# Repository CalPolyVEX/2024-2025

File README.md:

# 2024-2025

Code for 2024-2025 year

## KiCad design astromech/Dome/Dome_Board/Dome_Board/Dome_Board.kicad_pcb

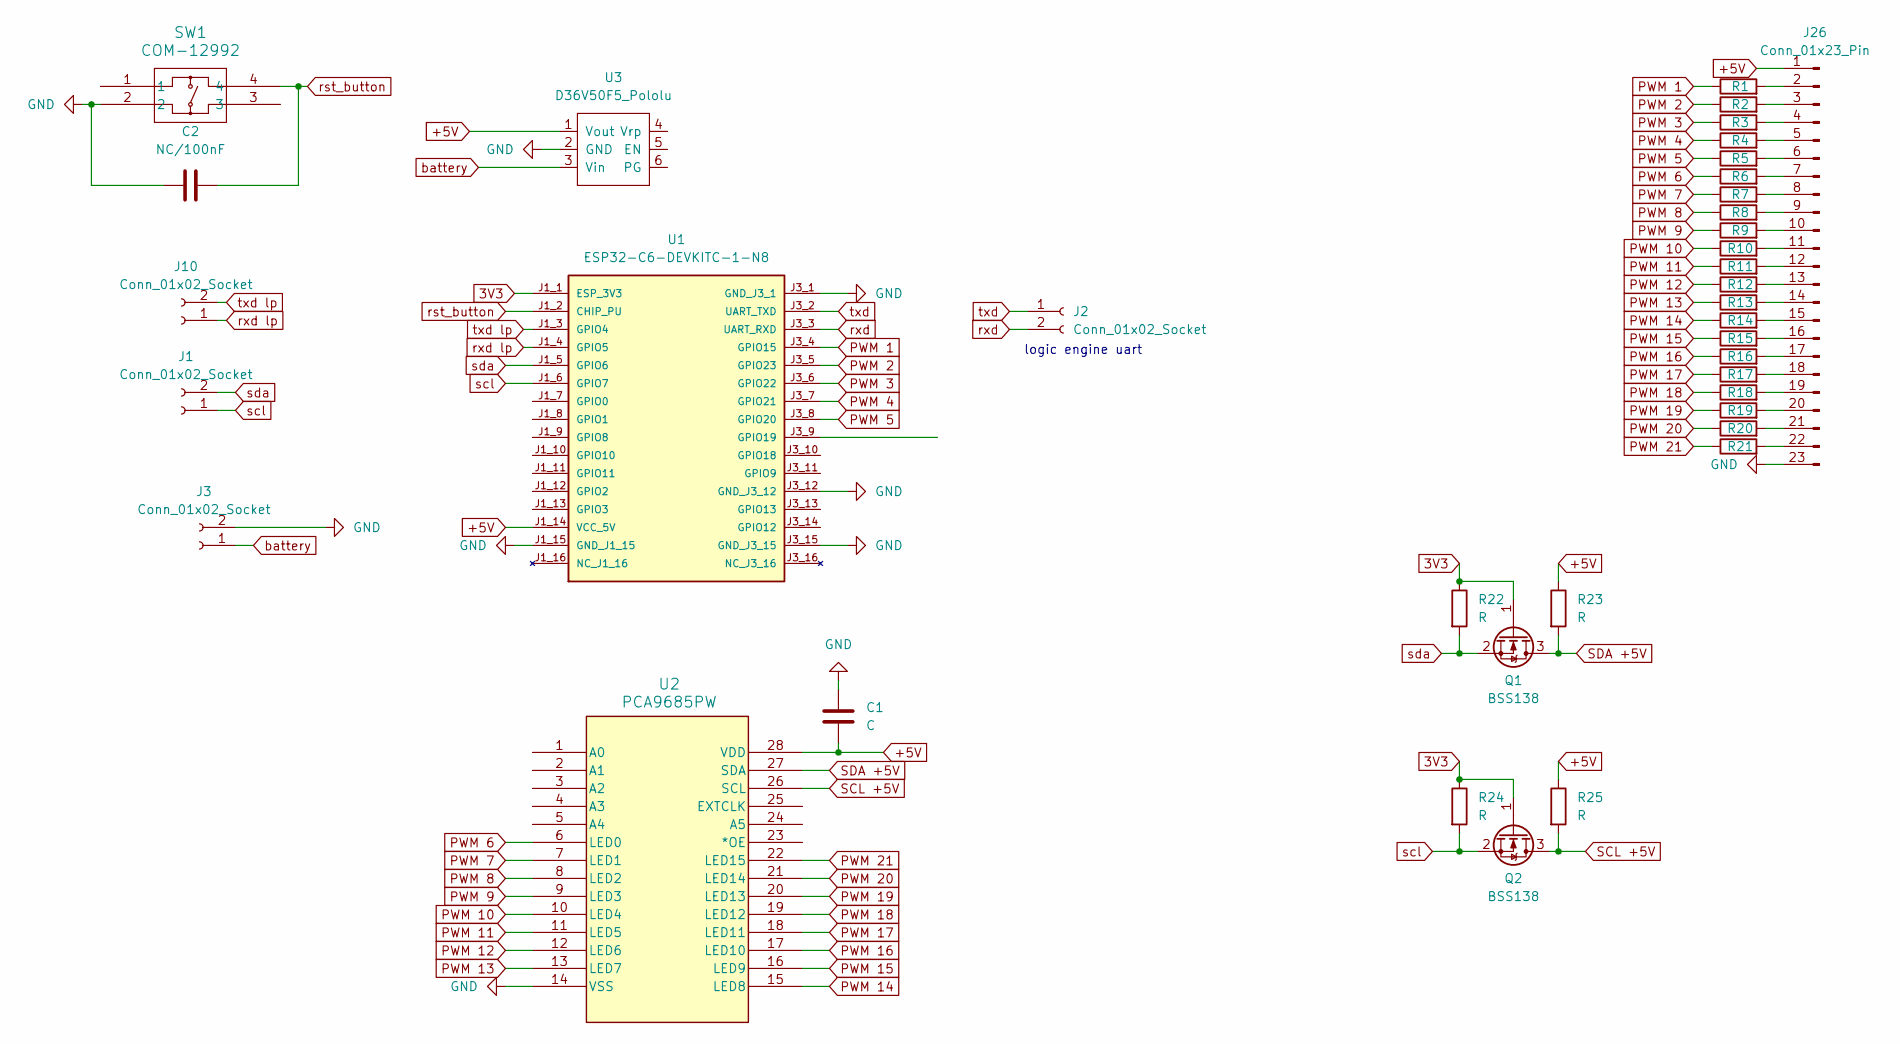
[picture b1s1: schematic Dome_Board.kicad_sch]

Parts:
C1: C; C_1206_3216Metric_Pad1.33x1.80mm_HandSolder
C2: NC/100nF; C_1206_3216Metric_Pad1.33x1.80mm_HandSolder
J1, J2, J3, J10: Conn_01x02_Socket; PinSocket_1x02_P1.27mm_Vertical
J26: Conn_01x23_Pin; PinHeader_1x23_P2.54mm_Vertical
Q1, Q2: BSS138; SOT-23
R1, R2, R3, R4, R5, R6, R7, R8, R9, R10, R11, R12, R13, R14, R15, R16, R17, R18, R19, R20, R21, R22, R23, R24, R25: R; R_1206_3216Metric_Pad1.30x1.75mm_HandSolder
SW1: COM-12992; COM-12992_SPK
U1: ESP32-C6-DEVKITC-1-N8; MODULE_ESP32-C6-DEVKITC-1-N8; PARTREV 1.3
U2: PCA9685PW; SOT361-1_NXP-M
U3: D36V50F5_Pololu

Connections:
3V3: Q1.1 (G), Q2.1 (G), R22.1, R24.1, U1.J1_1 (ESP_3V3)
+5V: C1.2, J26.1, R23.1, R25.1, U1.J1_14 (VCC_5V), U2.28 (VDD), U3.1 (Vout)
GND: C1.1, C2.1, J3.2, J26.23, SW1.2, U1.J1_15 (GND_J1_15), U1.J3_1 (GND_J3_1), U1.J3_12 (GND_J3_12), U1.J3_15 (GND_J3_15), U2.14 (VSS), U3.2 (GND)
unnamed: J26.2, R1.2
unnamed: J26.3, R2.2
unnamed: J26.4, R3.2
unnamed: J26.5, R4.2
unnamed: J26.6, R5.2
unnamed: J26.7, R6.2
unnamed: J26.8, R7.2
unnamed: J26.9, R8.2
unnamed: J26.10, R9.2
unnamed: J26.11, R10.2
unnamed: J26.12, R11.2
unnamed: J26.13, R12.2
unnamed: J26.14, R13.2
unnamed: J26.15, R14.2
unnamed: J26.16, R15.2
unnamed: J26.17, R16.2
unnamed: J26.18, R17.2
unnamed: J26.19, R18.2
unnamed: J26.20, R19.2
unnamed: J26.21, R20.2
unnamed: J26.22, R21.2
PWM 1: R1.1, U1.J3_4 (GPIO15)
PWM 2: R2.1, U1.J3_5 (GPIO23)
PWM 3: R3.1, U1.J3_6 (GPIO22)
PWM 4: R4.1, U1.J3_7 (GPIO21)
PWM 5: R5.1, U1.J3_8 (GPIO20)
PWM 6: R6.1, U2.6 (LED0)
PWM 7: R7.1, U2.7 (LED1)
PWM 8: R8.1, U2.8 (LED2)
PWM 9: R9.1, U2.9 (LED3)
PWM 10: R10.1, U2.10 (LED4)
PWM 11: R11.1, U2.11 (LED5)
PWM 12: R12.1, U2.12 (LED6)
PWM 13: R13.1, U2.13 (LED7)
PWM 14: R14.1, U2.15 (LED8)
PWM 15: R15.1, U2.16 (LED9)
PWM 16: R16.1, U2.17 (LED10)
PWM 17: R17.1, U2.18 (LED11)
PWM 18: R18.1, U2.19 (LED12)
PWM 19: R19.1, U2.20 (LED13)
PWM 20: R20.1, U2.21 (LED14)
PWM 21: R21.1, U2.22 (LED15)
SCL +5V: Q2.3 (D), R25.2, U2.26 (SCL)
SDA +5V: Q1.3 (D), R23.2, U2.27 (SDA)
battery: J3.1, U3.3 (Vin)
rst_button: C2.2, SW1.4, U1.J1_2 (CHIP_PU)
rxd: J2.2, U1.J3_3 (UART_RXD)
rxd lp: J10.1, U1.J1_4 (GPIO5)
scl: J1.1, Q2.2 (S), R24.2, U1.J1_6 (GPIO7)
sda: J1.2, Q1.2 (S), R22.2, U1.J1_5 (GPIO6)
txd: J2.1, U1.J3_2 (UART_TXD)
txd lp: J10.2, U1.J1_3 (GPIO4)

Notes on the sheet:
logic engine uart

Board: 2 copper layers, 38 parts (0 on the bottom side), 55 nets, no tracks yet.

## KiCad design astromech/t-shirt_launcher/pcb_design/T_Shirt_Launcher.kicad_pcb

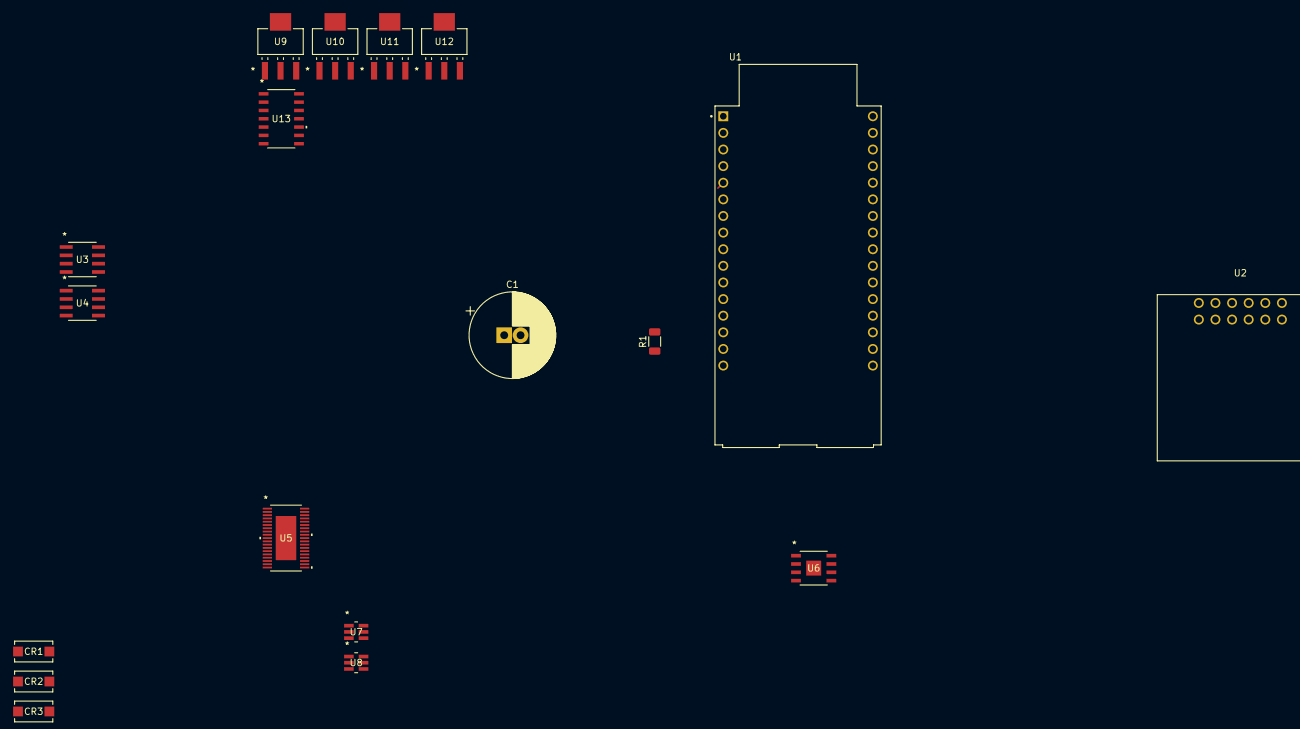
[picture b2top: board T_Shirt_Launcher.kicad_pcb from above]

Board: 2 copper layers, 18 parts (0 on the bottom side), 2 nets.

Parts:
C1: 100uF; CP_Radial_D13.0mm_P2.50mm
CR1, CR2, CR3: MURA120T3G; DIODE_TVS1SMAS5_4P57X2P92_ONS
R1: R; R_1206_3216Metric
U1: ESP32-C6-DEVKITC-1-N8; MODULE_ESP32-C6-DEVKITC-1-N8
U2: D36V50F5_Pololu
U3, U4: ADA4510-2ARZ; R-8_ADI
U5: MAX22203AUU+; 21-0714_U38E&plus_3C_ADI
U6: ADP3634ARDZ; RD_8_1_ADI
U7, U8: SN74LVC1G19DBVR; DBV6
U9, U10, U11, U12: NTF3055L108T1G; SOT-223_3P7X6P7_ONS
U13: MC74HCU04ADG; SOIC-14_NB_ONS

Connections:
unnamed: C1.2, R1.2, U1.J1_15 (GND_J1_15)
unnamed: C1.1, R1.1, U1.J1_14 (VCC_5V)

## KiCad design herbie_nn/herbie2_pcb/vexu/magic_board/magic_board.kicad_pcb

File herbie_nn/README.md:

# Directory structure

```goal_nn``` - scripts for the goal neural network

```ground_detection``` - scripts for the ground boundary neural network

```localization_nn``` - scripts for the localization neural network

```multi_task``` - training scripts for multi-task version of neural network

```herbie2_pcb``` - PCB design and firmware

```ros``` - C++ ROS nodes and launch files

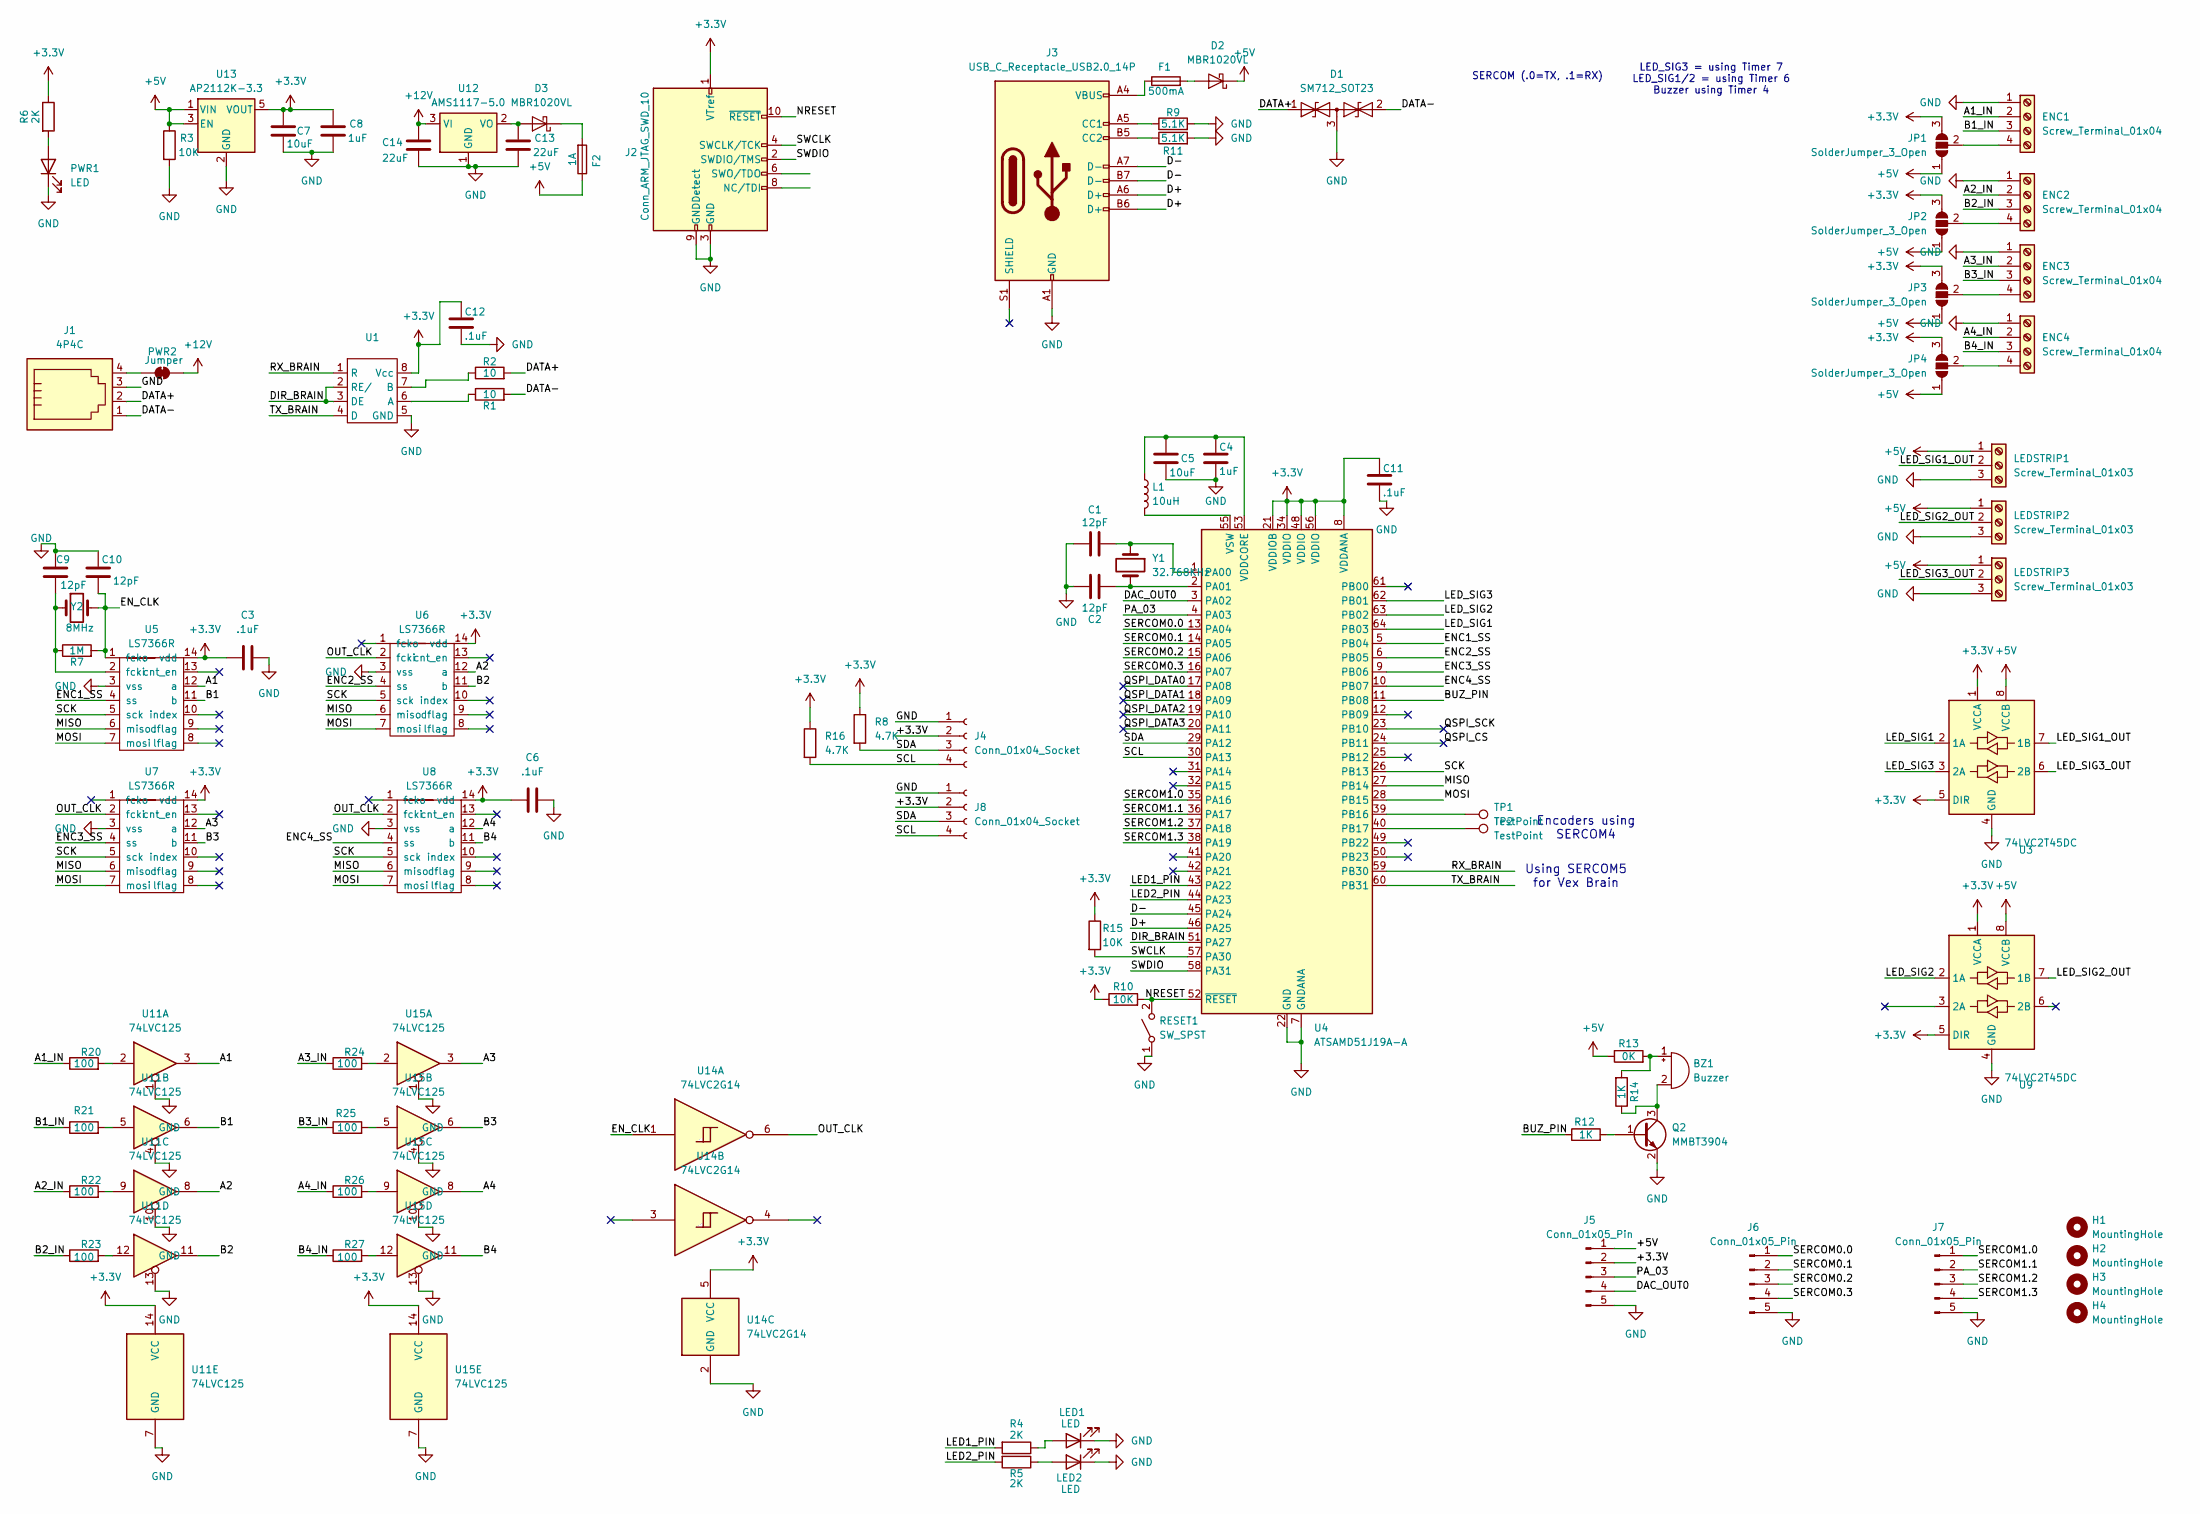
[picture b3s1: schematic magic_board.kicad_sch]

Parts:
BZ1: Buzzer; Buzzer_TDK_PS1240P02BT_D12.2mm_H6.5mm
C1, C2, C9, C10: 12pF; C_1206_3216Metric
C3, C6, C11, C12: .1uF; C_1206_3216Metric
C4, C8: 1uF; C_1206_3216Metric
C5, C7: 10uF; C_1206_3216Metric
C13, C14: 22uF; C_1206_3216Metric
D1: SM712_SOT23; SOT-23
D2, D3: MBR1020VL; D_SOD-123F
ENC1, ENC2, ENC3, ENC4: Screw_Terminal_01x04; TerminalBlock_Phoenix_MPT-0,5-4-2.54_1x04_P2.54mm_Horizontal
F1: 500mA; Fuse_1206_3216Metric
F2: 1A; Fuse_1206_3216Metric
H1, H2, H3, H4: MountingHole; MountingHole_3.2mm_M3_DIN965
J1: 4P4C; assman_rj9
J2: Conn_ARM_JTAG_SWD_10; PinSocket_2x05_P1.27mm_Vertical
J3: USB_C_Receptacle_USB2.0_14P; USB_C_Receptacle_GCT_USB4085
J4, J8: Conn_01x04_Socket; JST_SH_BM04B-SRSS-TB_1x04-1MP_P1.00mm_Vertical
J5, J6, J7: Conn_01x05_Pin; PinHeader_1x05_P2.54mm_Vertical
JP1, JP2, JP3, JP4: SolderJumper_3_Open; SolderJumper-3_P1.3mm_Open_Pad1.0x1.5mm
L1: 10uH; L_1206_3216Metric
LED1, LED2: LED; LED_1206_3216Metric
LEDSTRIP1, LEDSTRIP2, LEDSTRIP3: Screw_Terminal_01x03; TerminalBlock_Phoenix_MPT-0,5-3-2.54_1x03_P2.54mm_Horizontal
PWR1: LED; LED_1206_3216Metric
PWR2: Jumper; SolderJumper-2_P1.3mm_Open_Pad1.0x1.5mm
Q2: MMBT3904; SOT-23
R1, R2: 10; R_1206_3216Metric
R3, R10, R15: 10K; R_1206_3216Metric
R4, R5, R6: 2K; R_1206_3216Metric
R7: 1M; R_1206_3216Metric
R8, R16: 4.7K; R_1206_3216Metric
R9, R11: 5.1K; R_1206_3216Metric
R12, R14: 1K; R_1206_3216Metric
R13: 0K; R_1206_3216Metric
R20, R21, R22, R23, R24, R25, R26, R27: 100; R_1206_3216Metric
RESET1: SW_SPST; SW_Push_1P1T_NO_CK_KMR2
TP1, TP2: TestPoint; TestPoint_Pad_1.0x1.0mm
U1: SOIC-8_3.9x4.9mm_P1.27mm
U3, U9: 74LVC2T45DC; VSSOP-8_2.3x2mm_P0.5mm
U4: ATSAMD51J19A-A; TQFP-64_10x10mm_P0.5mm
U5, U6, U7, U8: LS7366R; SOIC-14_3.9x8.7mm_P1.27mm
U11, U15: 74LVC125; TSSOP-14_4.4x5mm_P0.65mm
U12: AMS1117-5.0; SOT-223-3_TabPin2
U13: AP2112K-3.3; SOT-23-5
U14: 74LVC2G14; TSOP-6_1.65x3.05mm_P0.95mm
Y1: 32.768KHz; Crystal_SMD_2012-2Pin_2.0x1.2mm_HandSoldering
Y2: 8MHz; Crystal_SMD_5032-2Pin_5.0x3.2mm

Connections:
+3.3V: C3.1, C6.1, C7.1, C8.1, C11.1, C12.1, J2.1 (VTref), J4.2, J5.2, J8.2, JP1.3 (B), JP2.3 (B), JP3.3 (B), JP4.3 (B), R6.1, R8.1, R10.1, R15.1, R16.1, U1.8 (Vcc), U3.1 (VCCA), U3.5 (DIR), U4.8 (VDDANA), U4.21 (VDDIOB), U4.34 (VDDIO), U4.48 (VDDIO), U4.56 (VDDIO), U5.14 (vdd), U6.14 (vdd), U7.14 (vdd), U8.14 (vdd), U9.1 (VCCA), U9.5 (DIR), U11.14 (VCC), U13.5 (VOUT), U14.5 (VCC), U15.14 (VCC)
+5V: D2.1 (K), F2.1, J5.1, JP1.1 (A), JP2.1 (A), JP3.1 (A), JP4.1 (A), LEDSTRIP1.1, LEDSTRIP2.1, LEDSTRIP3.1, R3.1, R13.1, U3.8 (VCCB), U9.8 (VCCB), U13.1 (VIN), U13.3 (EN)
+12V: C14.1, PWR2.2 (B), U12.3 (VI)
/A1: U5.12 (a), U11.3
/A1_IN: ENC1.2, R20.1
/A2: U6.12 (a), U11.8
/A2_IN: ENC2.2, R22.1
/A3: U7.12 (a), U15.3
/A3_IN: ENC3.2, R24.1
/A4: U8.12 (a), U15.8
/A4_IN: ENC4.2, R26.1
/B1: U5.11 (b), U11.6
/B1_IN: ENC1.3, R21.1
/B2: U6.11 (b), U11.11
/B2_IN: ENC2.3, R23.1
/B3: U7.11 (b), U15.6
/B3_IN: ENC3.3, R25.1
/B4: U8.11 (b), U15.11
/B4_IN: ENC4.3, R27.1
/BUZ_PIN: R12.1, U4.11 (PB08)
/D+: J3.A6 (D+), J3.B6 (D+), U4.46 (PA25)
/D-: J3.A7 (D-), J3.B7 (D-), U4.45 (PA24)
/DAC_OUT0: J5.4, U4.3 (PA02)
/DATA+: D1.1 (A1), J1.2, R2.2
/DATA-: D1.2 (A2), J1.1, R1.2
/DIR_BRAIN: U1.2 (RE/), U1.3 (DE), U4.51 (PA27)
/ENC1_SS: U4.5 (PB04), U5.4 (ss)
/ENC2_SS: U4.6 (PB05), U6.4 (ss)
/ENC3_SS: U4.9 (PB06), U7.4 (ss)
/ENC4_SS: U4.10 (PB07), U8.4 (ss)
/EN_CLK: C10.2, R7.2, U5.1 (fcko), U14.1, Y2.2
/LED1_PIN: R4.2, U4.43 (PA22)
/LED2_PIN: R5.2, U4.44 (PA23)
/LED_SIG1: U3.2 (1A), U4.64 (PB03)
/LED_SIG1_OUT: LEDSTRIP1.2, U3.7 (1B)
/LED_SIG2: U4.63 (PB02), U9.2 (1A)
/LED_SIG2_OUT: LEDSTRIP2.2, U9.7 (1B)
/LED_SIG3: U3.3 (2A), U4.62 (PB01)
/LED_SIG3_OUT: LEDSTRIP3.2, U3.6 (2B)
/MISO: U4.27 (PB14), U5.6 (miso), U6.6 (miso), U7.6 (miso), U8.6 (miso)
/MOSI: U4.28 (PB15), U5.7 (mosi), U6.7 (mosi), U7.7 (mosi), U8.7 (mosi)
/NRESET: J2.10 (~RESET), R10.2, RESET1.2 (B), U4.52 (~RESET)
/OUT_CLK: U6.2 (fcki), U7.2 (fcki), U8.2 (fcki), U14.6
/PA_03: J5.3, U4.4 (PA03)
/QSPI_CS: U4.24 (PB11)
/QSPI_DATA0: U4.17 (PA08)
/QSPI_DATA1: U4.18 (PA09)
/QSPI_DATA2: U4.19 (PA10)
/QSPI_DATA3: U4.20 (PA11)
/QSPI_SCK: U4.23 (PB10)
/RX_BRAIN: U1.1 (R), U4.59 (PB30)
/SCK: U4.26 (PB13), U5.5 (sck), U6.5 (sck), U7.5 (sck), U8.5 (sck)
/SCL: J4.4, J8.4, R16.2, U4.30 (PA13)
/SDA: J4.3, J8.3, R8.2, U4.29 (PA12)
/SERCOM0.0: J6.1, U4.13 (PA04)
/SERCOM0.1: J6.2, U4.14 (PA05)
/SERCOM0.2: J6.3, U4.15 (PA06)
/SERCOM0.3: J6.4, U4.16 (PA07)
/SERCOM1.0: J7.1, U4.35 (PA16)
/SERCOM1.1: J7.2, U4.36 (PA17)
/SERCOM1.2: J7.3, U4.37 (PA18)
/SERCOM1.3: J7.4, U4.38 (PA19)
/SWCLK: J2.4 (SWCLK/TCK), R15.2, U4.57 (PA30)
/SWDIO: J2.2 (SWDIO/TMS), U4.58 (PA31)
/TX_BRAIN: U1.4 (D), U4.60 (PB31)
GND: C1.1, C2.1, C3.2, C4.2, C5.2, C6.2, C7.2, C8.2, C9.1, C10.1, C11.2, C12.2, C13.2, C14.2, D1.3 (common), ENC1.1, ENC2.1, ENC3.1, ENC4.1, J1.3, J2.3 (GND), J2.5 (GND), J2.9 (GNDDetect), J3.A1 (GND), J3.A12 (GND), J3.B1 (GND), J3.B12 (GND), J4.1, J5.5, J6.5, J7.5, J8.1, LED1.1 (K), LED2.1 (K), LEDSTRIP1.3, LEDSTRIP2.3, LEDSTRIP3.3, PWR1.1 (K), Q2.2 (E), R3.2, R9.2, R11.2, RESET1.1 (A), U1.5 (GND), U3.4 (GND), U4.7 (GNDANA), U4.22 (GND), U4.33 (GND), U4.47 (GND), U4.54 (GND), U5.3 (vss), U6.3 (vss), U7.3 (vss), U8.3 (vss), U9.4 (GND), U11.1, U11.4, U11.7 (GND), U11.10, U11.13, U12.1 (GND), U13.2 (GND), U14.2 (GND), U15.1, U15.4, U15.7 (GND), U15.10, U15.13
unnamed: BZ1.1 (+), R13.2, R14.2
unnamed: BZ1.2 (-), Q2.3 (C), R14.1
unnamed: D2.2 (A), F1.2
unnamed: C13.1, D3.2 (A), U12.2 (VO)
unnamed: D3.1 (K), F2.2
unnamed: ENC1.4, JP1.2 (C)
unnamed: ENC2.4, JP2.2 (C)
unnamed: ENC3.4, JP3.2 (C)
unnamed: ENC4.4, JP4.2 (C)
unnamed: F1.1, J3.A4 (VBUS), J3.A9 (VBUS), J3.B4 (VBUS), J3.B9 (VBUS)
unnamed: J3.A5 (CC1), R9.1
unnamed: J3.B5 (CC2), R11.1
unnamed: LED1.2 (A), R4.1
unnamed: LED2.2 (A), R5.1
unnamed: PWR1.2 (A), R6.2
unnamed: J1.4, PWR2.1 (A)
unnamed: Q2.1 (B), R12.2
unnamed: R20.2, U11.2
unnamed: R21.2, U11.5
unnamed: R22.2, U11.9
unnamed: R23.2, U11.12
unnamed: R24.2, U15.2
unnamed: R25.2, U15.5
unnamed: R26.2, U15.9
unnamed: R27.2, U15.12
unnamed: R1.1, U1.6 (A)
unnamed: R2.1, U1.7 (B)
unnamed: C1.2, U4.1 (PA00), Y1.1
unnamed: C2.2, U4.2 (PA01), Y1.2
unnamed: TP1.1, U4.39 (PB16)
unnamed: TP2.1, U4.40 (PB17)
unnamed: C4.1, C5.1, L1.1, U4.53 (VDDCORE)
unnamed: L1.2, U4.55 (VSW)
unnamed: C9.2, R7.1, U5.2 (fcki), Y2.1

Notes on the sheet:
Encoders using SERCOM4
SERCOM (.0=TX, .1=RX)
LED_SIG3 = using Timer 7 LED_SIG1/2 = using Timer 6 Buzzer using Timer 4
Using SERCOM5 for Vex Brain

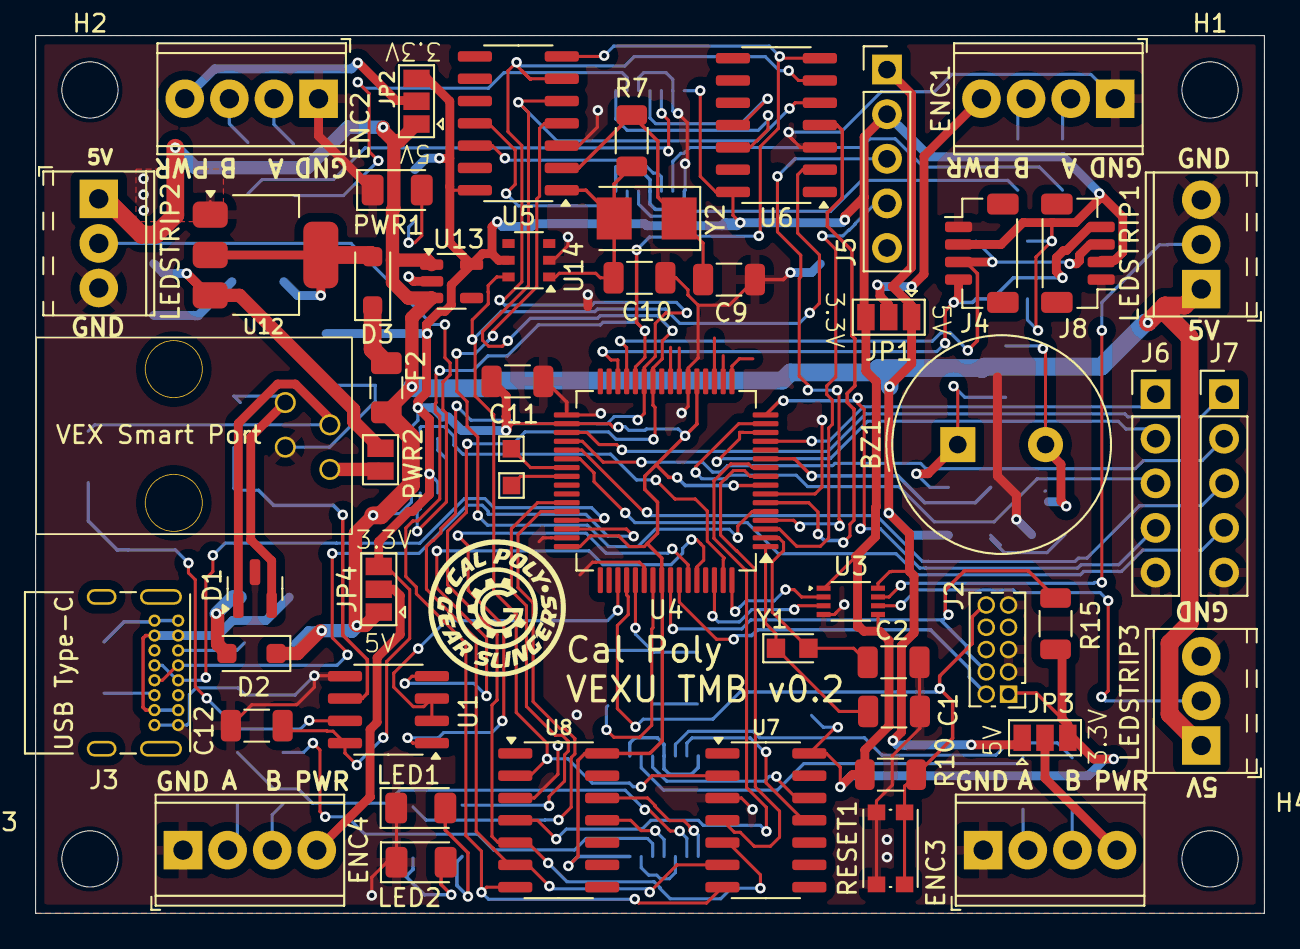
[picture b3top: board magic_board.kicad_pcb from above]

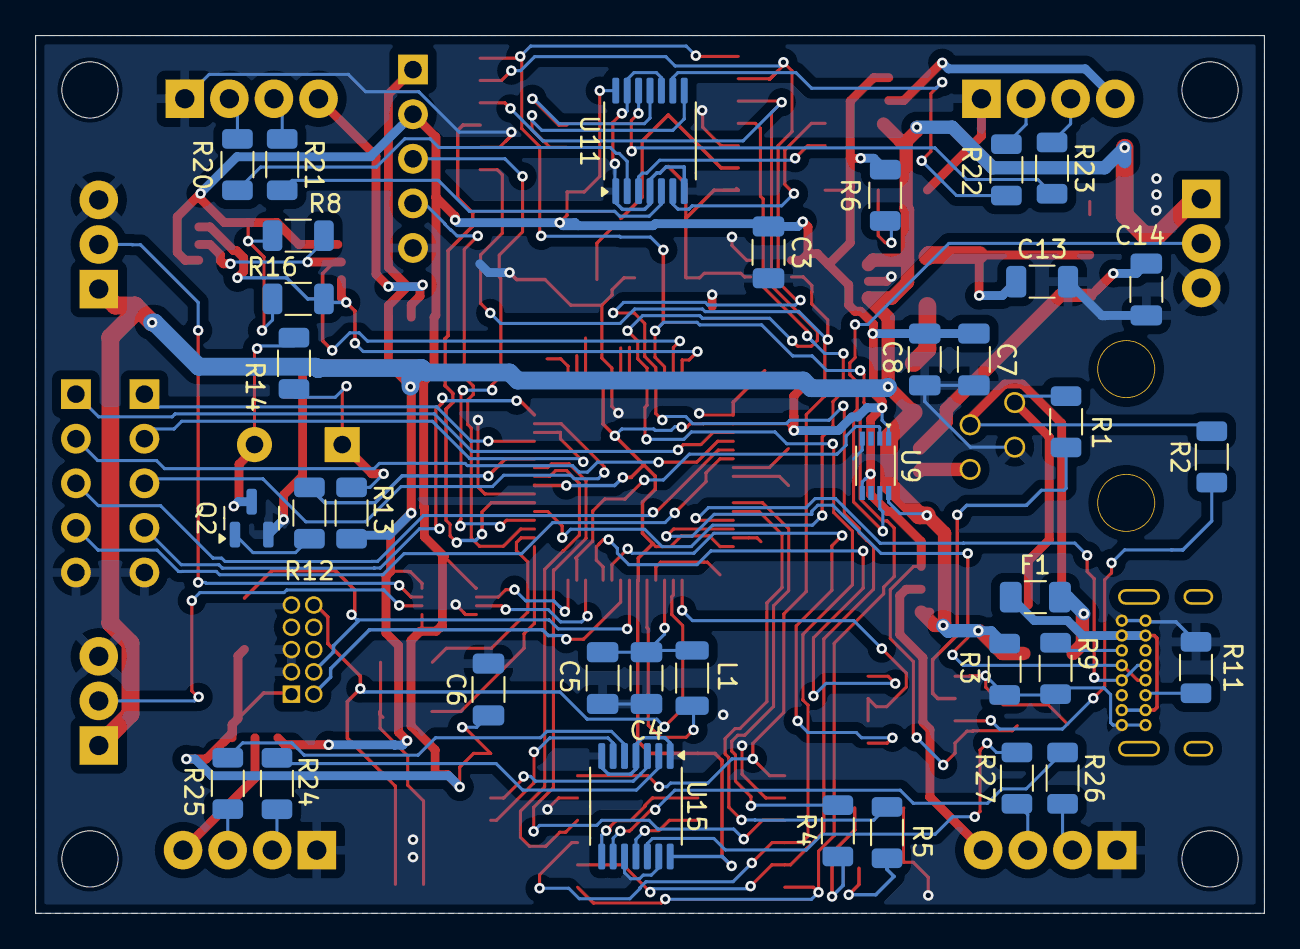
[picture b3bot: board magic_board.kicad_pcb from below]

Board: 2 copper layers, 70.0 x 50.0 mm, 91 parts (35 on the bottom side), 94 nets.

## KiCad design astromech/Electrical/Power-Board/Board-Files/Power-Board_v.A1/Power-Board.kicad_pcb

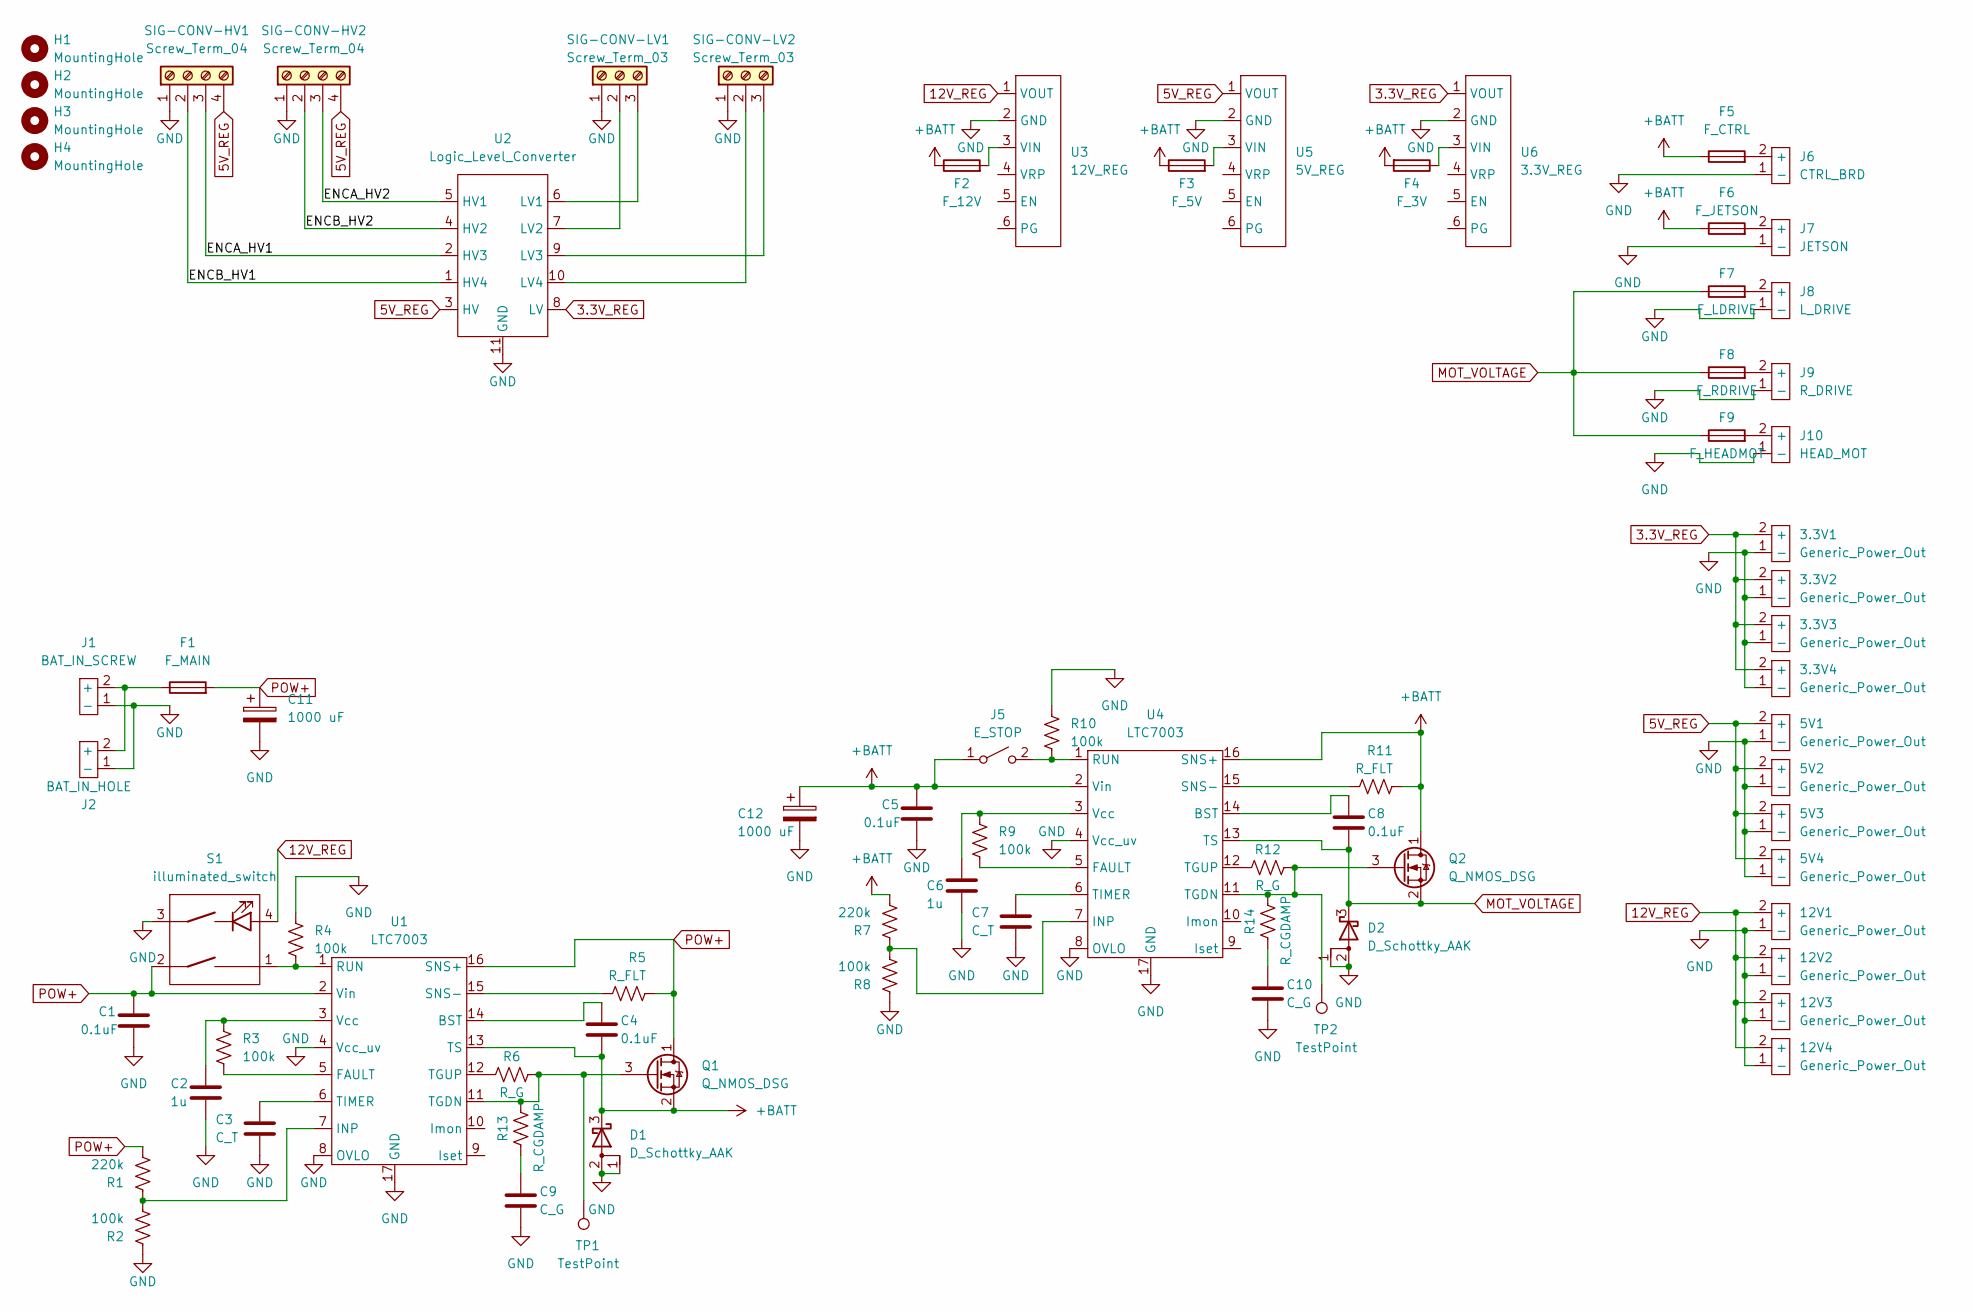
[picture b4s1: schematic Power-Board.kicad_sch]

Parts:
3.3V1, 3.3V2, 3.3V3, 3.3V4, 5V1, 5V2, 5V3, 5V4, 12V1, 12V2, 12V3, 12V4: Generic_Power_Out; Phoenix-1935161
C1, C4, C5, C8: 0.1uF; C_1206_3216Metric_Pad1.33x1.80mm_HandSolder
C2, C6: 1u; C_1206_3216Metric_Pad1.33x1.80mm_HandSolder
C3, C7: C_T; C_1206_3216Metric_Pad1.33x1.80mm_HandSolder
C9, C10: C_G; C_1206_3216Metric_Pad1.33x1.80mm_HandSolder
C11, C12: 1000 uF; CP_Radial_D10.0mm_P5.00mm
D1, D2: D_Schottky_AAK; TO-277A
F1: F_MAIN; Fuseholder_Blade_Mini_Keystone_3568
F2: F_12V; Generic-Fuse
F3: F_5V; Generic-Fuse
F4: F_3V; Generic-Fuse
F5: F_CTRL; Generic-Fuse
F6: F_JETSON; Generic-Fuse
F7: F_LDRIVE; 10.2mm fuse
F8: F_RDRIVE; 10.2mm fuse
F9: F_HEADMOT; Generic-Fuse
H1, H2, H3, H4: MountingHole; MountingHole_3.2mm_M3_ISO7380
J1: BAT_IN_SCREW; Molex-393900102
J2: BAT_IN_HOLE; 10AWG-Power-In
J5: E_STOP; Phoenix-1935161
J6: CTRL_BRD; Phoenix-1935161
J7: JETSON; Phoenix-1935161
J8: L_DRIVE; Phoenix-1935161
J9: R_DRIVE; Phoenix-1935161
J10: HEAD_MOT; Phoenix-1935161
Q1, Q2: Q_NMOS_DSG; NTMTS0D6N04CLTXG
R1, R7: 220k; R_1206_3216Metric_Pad1.30x1.75mm_HandSolder
R2, R3, R4, R8, R9, R10: 100k; R_1206_3216Metric_Pad1.30x1.75mm_HandSolder
R5, R11: R_FLT; R_1206_3216Metric_Pad1.30x1.75mm_HandSolder
R6, R12: R_G; R_1206_3216Metric_Pad1.30x1.75mm_HandSolder
R13, R14: R_CGDAMP; R_1206_3216Metric_Pad1.30x1.75mm_HandSolder
S1: illuminated_switch; Phoenix-1935187
SIG-CONV-HV1, SIG-CONV-HV2: Screw_Term_04; Phoenix-1935187
SIG-CONV-LV1, SIG-CONV-LV2: Screw_Term_03; Phoenix-1935174
TP1, TP2: TestPoint; TestPoint_Pad_D2.0mm
U1, U4: LTC7003
U2: Logic_Level_Converter; Sparkfun-Level-shifter
U3: 12V_REG; D36V50Fx
U5: 5V_REG; D36V50Fx
U6: 3.3V_REG; D36V50Fx

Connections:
3.3V_REG: 3.3V1.2 (+), 3.3V2.2 (+), 3.3V3.2 (+), 3.3V4.2 (+), U2.8 (LV), U6.1 (VOUT)
5V_REG: 5V1.2 (+), 5V2.2 (+), 5V3.2 (+), 5V4.2 (+), SIG-CONV-HV1.4, SIG-CONV-HV2.4, U2.3 (HV), U5.1 (VOUT)
12V_REG: 12V1.2 (+), 12V2.2 (+), 12V3.2 (+), 12V4.2 (+), S1.4, U3.1 (VOUT)
+BATT: C4.2, C5.1, C12.1, D1.3 (K), F2.1, F3.1, F4.2, F5.1, F6.1, J5.1 (A), Q1.2 (S), Q2.1 (D), R7.2, R11.2, U1.13 (TS), U4.2 (Vin), U4.16 (SNS+)
/ENCA_HV1: SIG-CONV-HV1.3, U2.2 (HV3)
/ENCA_HV2: SIG-CONV-HV2.3, U2.5 (HV1)
/ENCB_HV1: SIG-CONV-HV1.2, U2.1 (HV4)
/ENCB_HV2: SIG-CONV-HV2.2, U2.4 (HV2)
GND: 3.3V1.1 (-), 3.3V2.1 (-), 3.3V3.1 (-), 3.3V4.1 (-), 5V1.1 (-), 5V2.1 (-), 5V3.1 (-), 5V4.1 (-), 12V1.1 (-), 12V2.1 (-), 12V3.1 (-), 12V4.1 (-), C1.2, C2.2, C3.2, C5.2, C6.2, C7.2, C9.2, C10.2, C11.2, C12.2, D1.1 (A), D1.2 (A), D2.1 (A), D2.2 (A), J1.1 (-), J2.1 (-), J6.1 (-), J7.1 (-), J8.1 (-), J9.1 (-), J10.1 (-), R2.1, R4.1, R8.1, R10.1, S1.3, SIG-CONV-HV1.1, SIG-CONV-HV2.1, SIG-CONV-LV1.1, SIG-CONV-LV2.1, U1.4 (Vcc_uv), U1.8 (OVLO), U1.17 (GND), U2.11 (GND), U3.2 (GND), U4.4 (Vcc_uv), U4.8 (OVLO), U4.17 (GND), U5.2 (GND), U6.2 (GND)
MOT_VOLTAGE: C8.2, D2.3 (K), F7.1, F8.1, F9.1, Q2.2 (S), U4.13 (TS)
unnamed: C2.1, R3.1, U1.3 (Vcc)
unnamed: C3.1, U1.6 (TIMER)
unnamed: C4.1, U1.14 (BST)
unnamed: C6.1, R9.1, U4.3 (Vcc)
unnamed: C7.1, U4.6 (TIMER)
unnamed: C8.1, U4.14 (BST)
unnamed: C9.1, R13.1
unnamed: C10.1, R14.1
unnamed: F1.1, J1.2 (+), J2.2 (+)
unnamed: F2.2, U3.3 (VIN)
unnamed: F3.2, U5.3 (VIN)
unnamed: F4.1, U6.3 (VIN)
unnamed: F5.2, J6.2 (+)
unnamed: F6.2, J7.2 (+)
unnamed: F7.2, J8.2 (+)
unnamed: F8.2, J9.2 (+)
unnamed: F9.2, J10.2 (+)
unnamed: J5.2 (B), R10.2, U4.1 (RUN)
unnamed: Q1.3 (G), R6.2, R13.2, TP1.1, U1.11 (TGDN)
unnamed: Q2.3 (G), R12.2, R14.2, TP2.1, U4.11 (TGDN)
unnamed: R1.1, R2.2, U1.7 (INP)
unnamed: R3.2, U1.5 (FAULT)
unnamed: R4.2, S1.1, U1.1 (RUN)
unnamed: R5.1, U1.15 (SNS-)
unnamed: R6.1, U1.12 (TGUP)
unnamed: R7.1, R8.2, U4.7 (INP)
unnamed: R9.2, U4.5 (FAULT)
unnamed: R11.1, U4.15 (SNS-)
unnamed: R12.1, U4.12 (TGUP)
unnamed: SIG-CONV-LV1.2, U2.7 (LV2)
unnamed: SIG-CONV-LV1.3, U2.6 (LV1)
unnamed: SIG-CONV-LV2.2, U2.10 (LV4)
unnamed: SIG-CONV-LV2.3, U2.9 (LV3)
POW+: C1.1, C11.1, F1.2, Q1.1 (D), R1.2, R5.2, S1.2, U1.2 (Vin), U1.16 (SNS+)

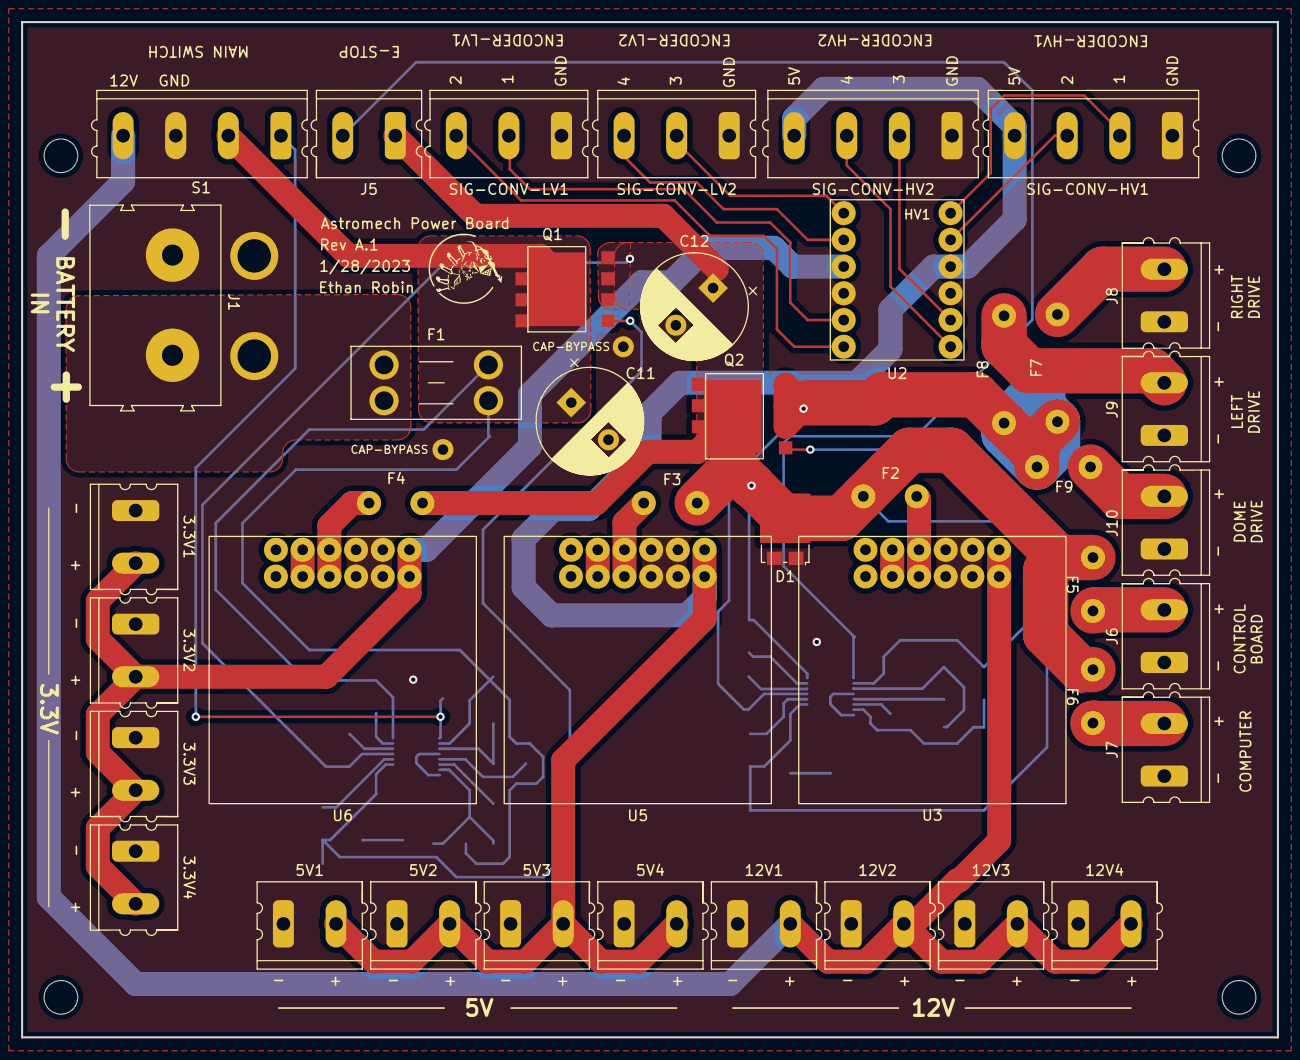
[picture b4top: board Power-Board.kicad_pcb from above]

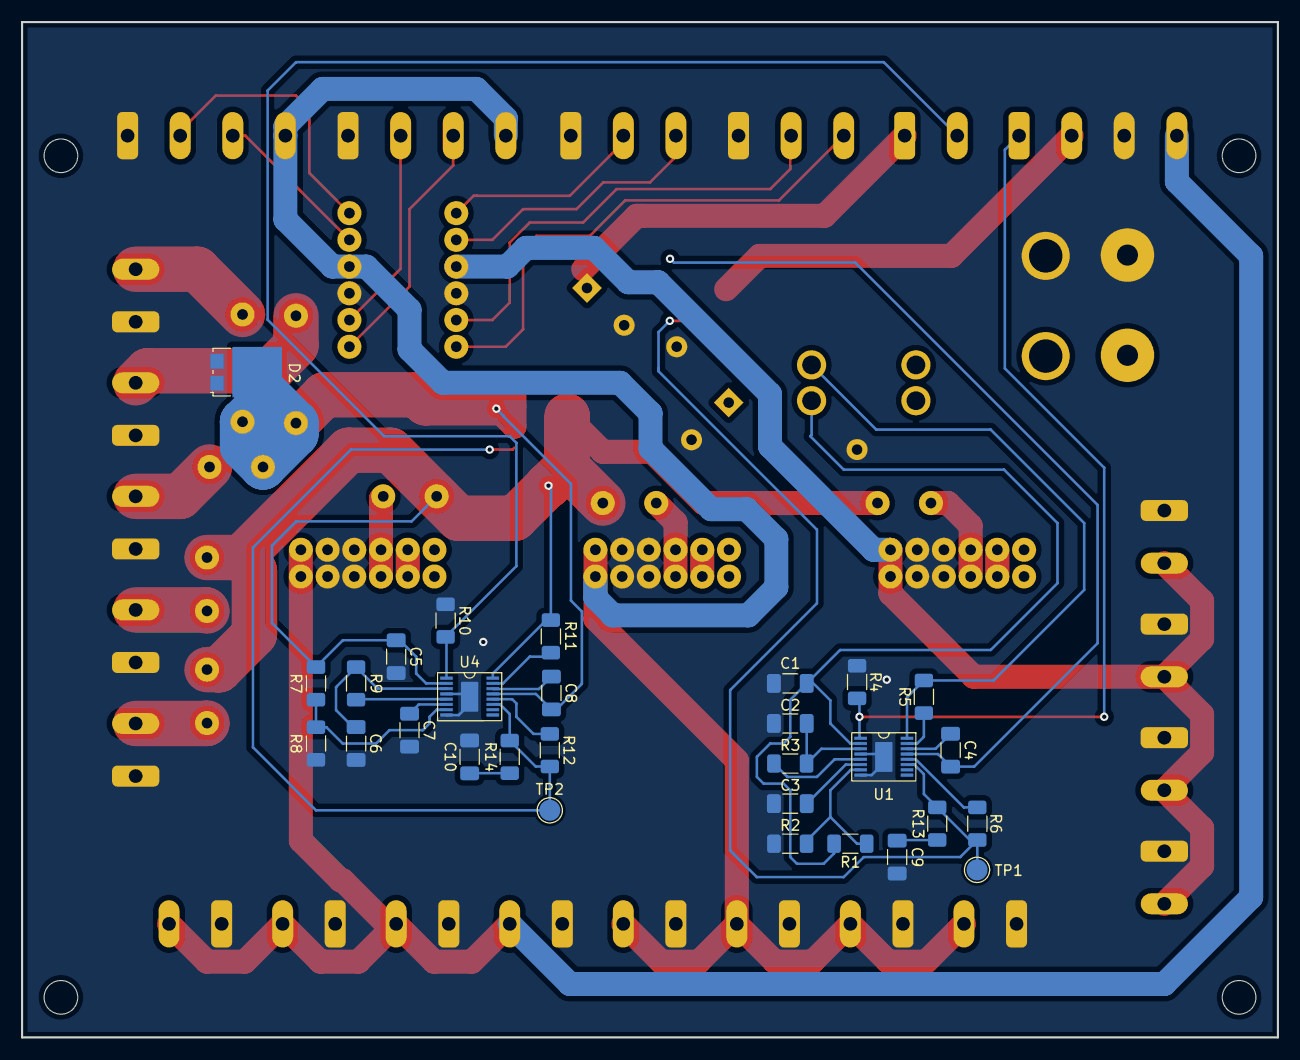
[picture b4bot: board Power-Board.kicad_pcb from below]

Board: 2 copper layers, 119.4 x 96.5 mm, 76 parts (29 on the bottom side), 44 nets.
